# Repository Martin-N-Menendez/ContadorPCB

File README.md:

# ContadorPCB

ContadorDePasajeros = Contador con ESP8266-01

Contador12 = Contador con ESP8266-12E

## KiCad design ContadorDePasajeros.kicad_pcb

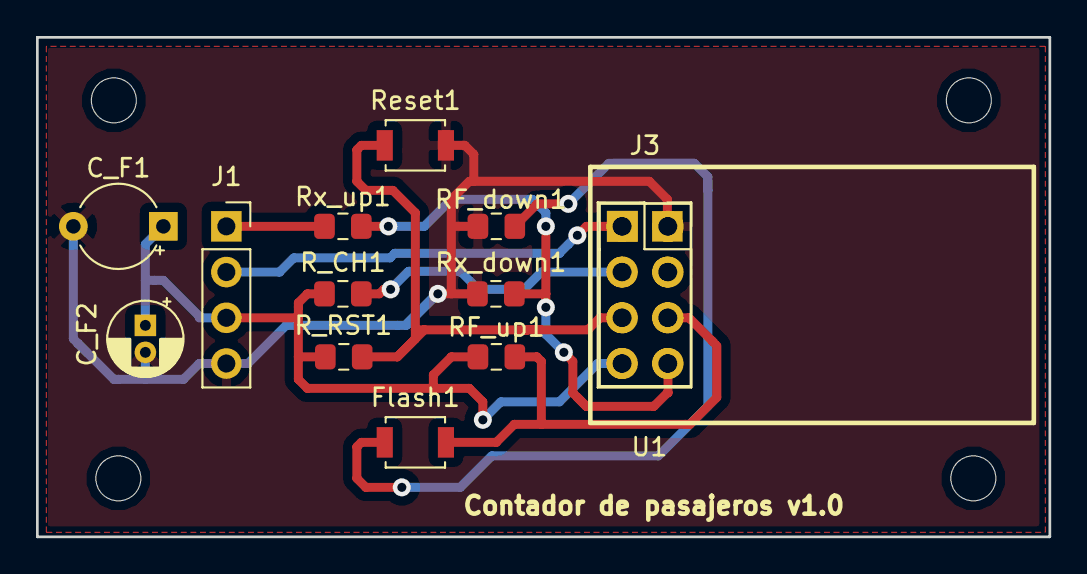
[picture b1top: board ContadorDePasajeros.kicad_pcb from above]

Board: 2 copper layers, 56.2 x 27.8 mm, 17 parts (0 on the bottom side), 10 nets.

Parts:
C_F1: 100n; CP_Radial_Tantal_D4.5mm_P5.00mm
C_F2: 100u; CP_Radial_D4.0mm_P1.50mm
Flash1: Jumper; SW_SPST_B3U-1000P
J1: Conector_in; PinSocket_1x04_P2.54mm_Vertical
J3: Conector_esp; PinSocket_2x04_P2.54mm_Vertical
MH1, MH2, MH3, MH4: MountingHole; MountingHole_2.5mm
RF_down1: 470; R_0805_2012Metric_Pad1.15x1.40mm_HandSolder
RF_up1: 3k3; R_0805_2012Metric_Pad1.15x1.40mm_HandSolder
R_CH1: 3k3; R_0805_2012Metric_Pad1.15x1.40mm_HandSolder
R_RST1: 3k3; R_0805_2012Metric_Pad1.15x1.40mm_HandSolder
Reset1: Jumper; SW_SPST_B3U-1000P
Rx_down1: 2k; R_0805_2012Metric_Pad1.15x1.40mm_HandSolder
Rx_up1: 1k; R_0805_2012Metric_Pad1.15x1.40mm_HandSolder
U1: ESP01; ESP-01

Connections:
CHA: J3.4, R_CH1.1, U1.3
G0A: Flash1.1, J3.5, RF_up1.2, U1.6
G2A: J3.3, U1.4
GNA: C_F1.2, C_F2.2, J1.4, J3.1, RF_down1.2, Reset1.2, Rx_down1.2, U1.2
unnamed: Flash1.2, RF_down1.1
RSA: J3.6, R_RST1.1, Reset1.1, U1.5
RXA: J3.7, Rx_down1.1, Rx_up1.2, U1.8
Rx: J1.1, Rx_up1.1
TXA: J1.2, J3.2, U1.1
VCA: C_F1.1, C_F2.1, J1.3, J3.8, RF_up1.1, R_CH1.2, R_RST1.2, U1.7

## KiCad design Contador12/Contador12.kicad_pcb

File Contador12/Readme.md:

Contador de pasajeros con ESP12

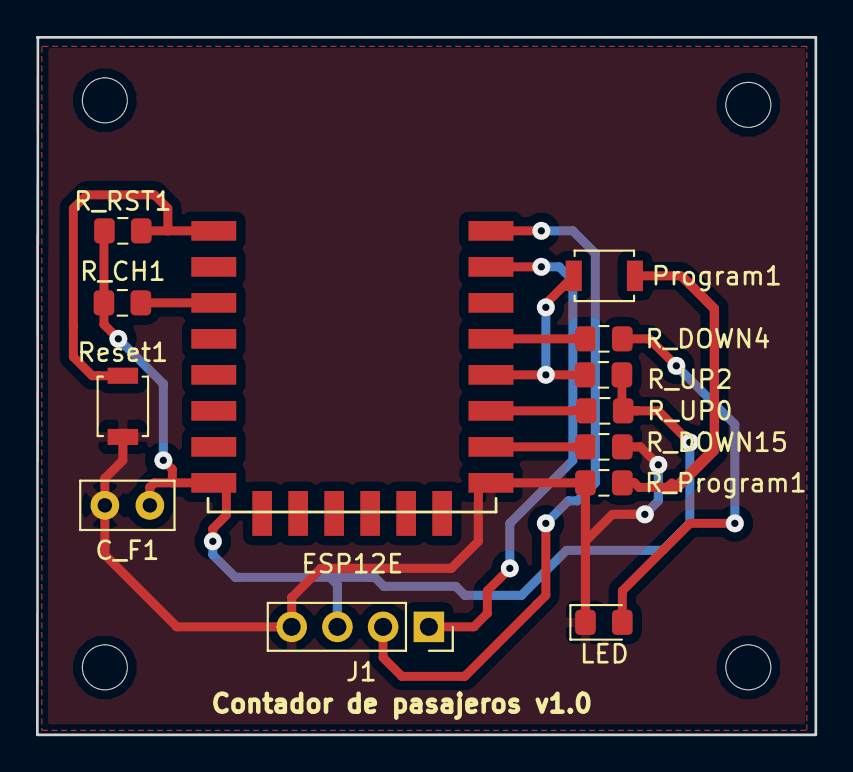
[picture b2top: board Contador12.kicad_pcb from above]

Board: 2 copper layers, 43.2 x 38.8 mm, 17 parts (0 on the bottom side), 12 nets.

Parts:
C_F1: 100n; C_Disc_D5.0mm_W2.5mm_P2.50mm
ESP12E: ESP-12E; ESP-12E_SMD
J1: Conector_ESP; PinSocket_1x04_P2.54mm_Vertical
LED: LED; LED_0805_2012Metric_Pad1.15x1.40mm_HandSolder
MH1, MH2, MH3, MH4: MountingHole; MountingHole_2.5mm
Program1: Jumper; SW_SPST_B3U-1000P
R_CH1: 10k; R_0805_2012Metric_Pad1.15x1.40mm_HandSolder
R_DOWN4: 470; R_0805_2012Metric_Pad1.15x1.40mm_HandSolder
R_DOWN15: 10k; R_0805_2012Metric_Pad1.15x1.40mm_HandSolder
R_Program1: 470; R_0805_2012Metric_Pad1.15x1.40mm_HandSolder
R_RST1: 10k; R_0805_2012Metric_Pad1.15x1.40mm_HandSolder
R_UP0, R_UP2: 10k; R_0805_2012Metric_Pad1.15x1.40mm_HandSolder
Reset1: Jumper; SW_SPST_B3U-1000P

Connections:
+3V3: C_F1.1, ESP12E.8, J1.3, R_CH1.2, R_RST1.1, R_UP0.1, R_UP2.2
GND: C_F1.2, ESP12E.9, J1.4, LED.1, R_DOWN15.2, R_Program1.2, Reset1.2
unnamed: LED.2, R_DOWN4.2
unnamed: ESP12E.12, Program1.1, R_UP0.2
unnamed: Program1.2, R_Program1.1
unnamed: ESP12E.3, R_CH1.1
unnamed: ESP12E.13, R_DOWN4.1
unnamed: ESP12E.10, R_DOWN15.1
unnamed: ESP12E.1, R_RST1.2, Reset1.1
unnamed: ESP12E.11, R_UP2.1
Rx: ESP12E.15, J1.1
Tx: ESP12E.16, J1.2

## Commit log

2018-10-12 Agregados los archivos
2018-10-13 delete
2018-10-13 Contador con ESP01
2018-10-13 Contador con ESP12
2018-10-14 Serigrafia y agujeros agregados
2018-10-14 Serigrafia, agujeros y ajustes
2018-10-16 Correcciones adrian
2018-10-19 Rotulo corregido
2018-10-20 Ajuste de ancho de pistas
2018-10-20 Power flag agregado
